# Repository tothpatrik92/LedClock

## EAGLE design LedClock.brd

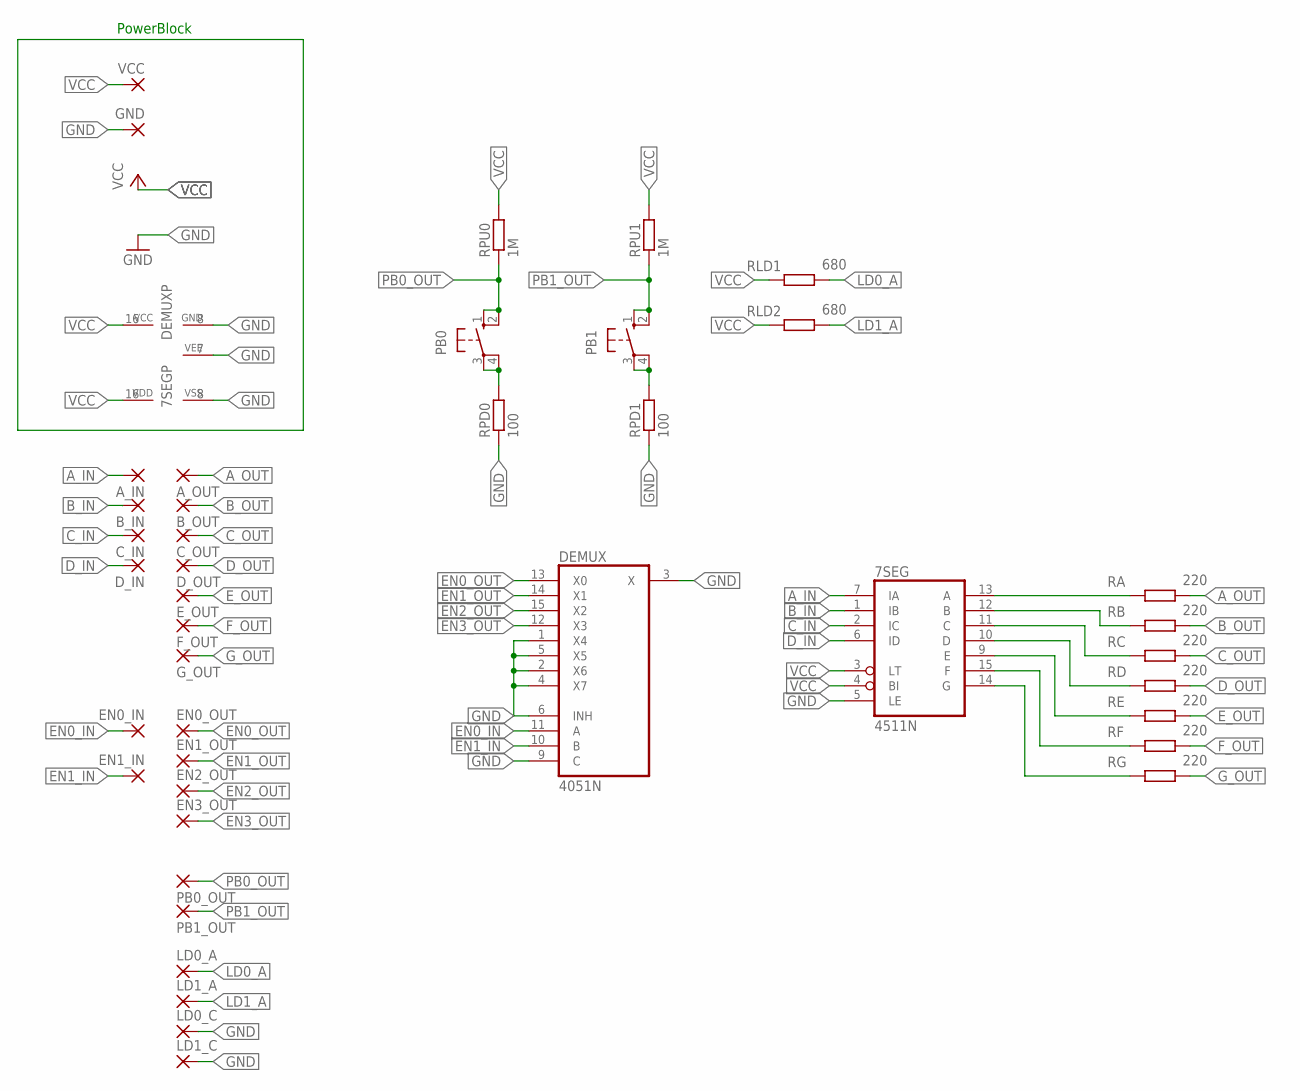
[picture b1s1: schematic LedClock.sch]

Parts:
7SEG: 4511N; DIL16
A_IN: 2,54/1,0
A_OUT: 2,54/1,0
B_IN: 2,54/1,0
B_OUT: 2,54/1,0
C_IN: 2,54/1,0
C_OUT: 2,54/1,0
DEMUX: 4051N; DIL16
D_IN: 2,54/1,0
D_OUT: 2,54/1,0
EN0_IN, EN0_OUT, EN1_IN, EN1_OUT, EN2_OUT, EN3_OUT: 2,54/1,0
E_OUT: 2,54/1,0
F_OUT: 2,54/1,0
GND: 2,54/1,0
G_OUT: 2,54/1,0
LD0_A, LD0_C, LD1_A, LD1_C: 2,54/1,0
PB0, PB1: 10-XX; B3F-10XX
PB0_OUT, PB1_OUT: 2,54/1,0
RA: 220; R1206
RB: 220; R1206
RC: 220; R1206
RD: 220; R1206
RE: 220; R1206
RF: 220; R1206
RG: 220; R1206
RLD1, RLD2: 680; R1206
RPD0, RPD1: 100; R1206
RPU0, RPU1: 1M; R1206
VCC: 2,54/1,0

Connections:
A_IN: 7SEG.7 (IA), A_IN.1
A_OUT: A_OUT.1, RA.2
B_IN: 7SEG.1 (IB), B_IN.1
B_OUT: B_OUT.1, RB.2
C_IN: 7SEG.2 (IC), C_IN.1
C_OUT: C_OUT.1, RC.2
D_IN: 7SEG.6 (ID), D_IN.1
D_OUT: D_OUT.1, RD.2
EN0_IN: DEMUX.11 (A), EN0_IN.1
EN0_OUT: DEMUX.13 (X0), EN0_OUT.1
EN1_IN: DEMUX.10 (B), EN1_IN.1
EN1_OUT: DEMUX.14 (X1), EN1_OUT.1
EN2_OUT: DEMUX.15 (X2), EN2_OUT.1
EN3_OUT: DEMUX.12 (X3), EN3_OUT.1
E_OUT: E_OUT.1, RE.2
F_OUT: F_OUT.1, RF.2
GND: 7SEG.5 (LE), 7SEG.8 (VSS), DEMUX.1 (X4), DEMUX.2 (X6), DEMUX.3 (X), DEMUX.4 (X7), DEMUX.5 (X5), DEMUX.6 (INH), DEMUX.7 (VEE), DEMUX.8 (GND), DEMUX.9 (C), GND.1, LD0_C.1, LD1_C.1, RPD0.1, RPD1.1
G_OUT: G_OUT.1, RG.2
LD0_A: LD0_A.1, RLD1.2
LD1_A: LD1_A.1, RLD2.2
unnamed: PB1.3, PB1.4 (P1), RPD1.2
unnamed: PB0.3, PB0.4 (P1), RPD0.2
unnamed: 7SEG.13 (A), RA.1
unnamed: 7SEG.12 (B), RB.1
unnamed: 7SEG.11 (C), RC.1
unnamed: 7SEG.10 (D), RD.1
unnamed: 7SEG.9 (E), RE.1
unnamed: 7SEG.15 (F), RF.1
unnamed: 7SEG.14 (G), RG.1
PB0_OUT: PB0.1 (S), PB0.2 (S1), PB0_OUT.1, RPU0.1
PB1_OUT: PB1.1 (S), PB1.2 (S1), PB1_OUT.1, RPU1.1
VCC: 7SEG.3 (LT), 7SEG.4 (BI), 7SEG.16 (VDD), DEMUX.16 (VCC), RLD1.1, RLD2.1, RPU0.2, RPU1.2, VCC.1

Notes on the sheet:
PowerBlock

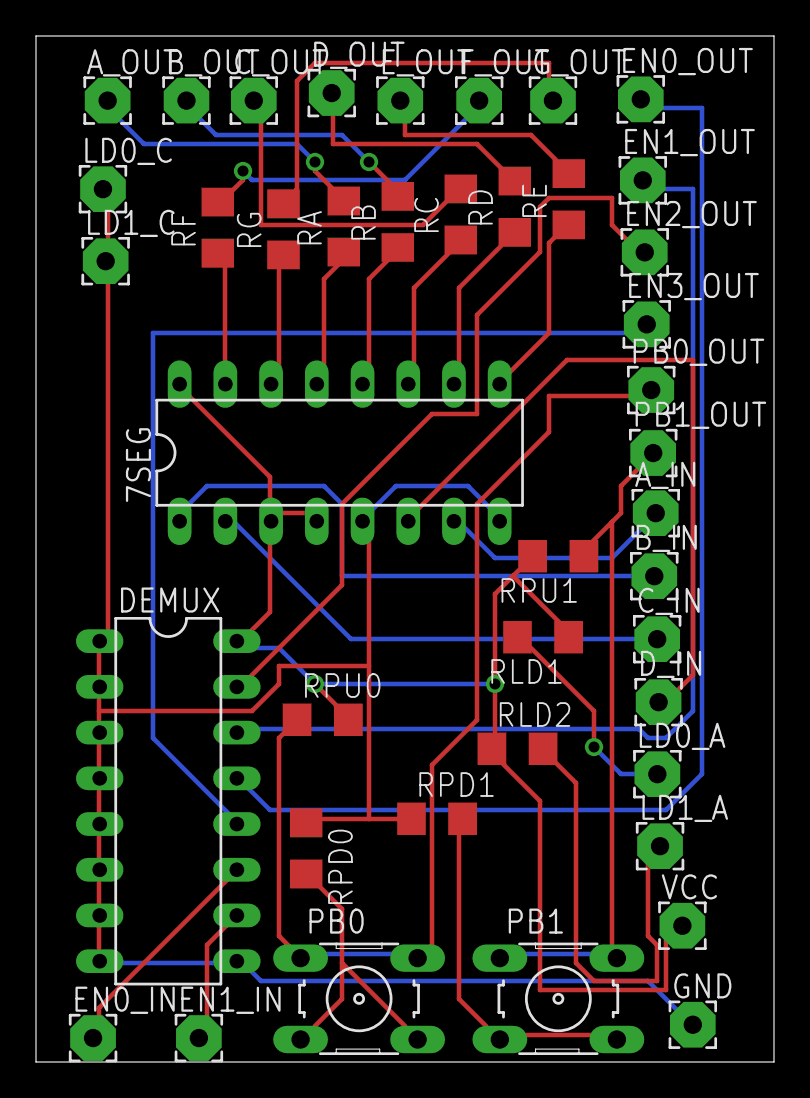
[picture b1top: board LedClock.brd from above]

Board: 2 copper layers, 41.0 x 57.0 mm, 42 parts (0 on the bottom side), 32 nets.

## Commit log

2020-11-10 Files are generated
2020-11-10 Adding components to schematic
2020-11-12 schematic v0. All parts are added.
2020-11-12 All parts are added. schematic_V0
2020-11-12 Add pcd design v0
2020-11-14 new sch, win10 reinstall
2020-11-14 Sch_v1. All parts are added.
